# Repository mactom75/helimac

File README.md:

<p align="center">
  <a href="https://helimac.pl/en/">
    <picture>
      <source media="(prefers-color-scheme: dark)" srcset="website/assets/img/logo-dark-600.webp">
      
    </picture>
  </a>
</p>

<p align="center"><b>Open-source single-seat electric helicopter</b><br>
coaxial rotors · weight-shift control · 400 V electric drive · built in the open</p>

<p align="center">
  🇬🇧 English · <a href="README.pl.md">🇵🇱 Polski</a> · 🌐 <a href="https://helimac.pl/en/">helimac.pl</a> · ▶️ <a href="https://www.youtube.com/@Helimac-pl">YouTube</a> · ☕ <a href="https://buycoffee.to/helimac">Support</a>
</p>

> **Current design: rev K — in design (update 26 Nov 2026: [motor B, rotor, drive, controls, inverter](docs/design-rev-K-2026-11-26.md)).** The machine was recalculated from scratch to cut the mass from 74.9 to ≈ 43.4 kg. Files in [`production/`](production/README.md) are **rev J2 — archive, do not build** (exception: MC-P inverter rev D1 is current). Rev K production packages will follow after stage 3 (CAD + drawings).

---

## Start here

| I want to… | Go to |
|---|---|
| 👀 **see the design** | [Design rev K](docs/design-rev-K.md) + [update 26 Nov](docs/design-rev-K-2026-11-26.md) · [drawings 26 Nov](docs/graphics/revK/2026-11-26/) · [graphics](docs/graphics/revK/) · [layout sketch](docs/graphics/HELIMAC_revK_szkic_ukladu.pdf) · [parameters](docs/parameters.md) · [website](https://helimac.pl/en/) |
| 📦 **download the files** | rev K: [calculations](calc/revK/), [drawings (PDF)](docs/graphics/revK/2026-11-26/), [blade templates (DXF)](hardware/blades/revK-templates/) · rev J2 (archive): [release](../../releases/latest), [production files](production/) · MC-P inverter rev D1 (current): [files](production/electronics/MC-P-inverter-revD1/) |
| 🛠️ **help build it** | [Open tasks (Issues)](../../issues) · [Discussions](../../discussions) · [How to contribute](CONTRIBUTING.md) |
| ▶️ **follow the build** | [YouTube @Helimac-pl](https://www.youtube.com/@Helimac-pl) · [build log](BUILD_LOG.md) · [roadmap](ROADMAP.md) |
| ☕ **support the project** | [buycoffee.to/helimac](https://buycoffee.to/helimac) — every coffee goes to parts and dynamometer tests |

> ⚠️ **Prototype in design — not an approved aircraft.** All values are calculated, not yet measured. Read [SAFETY.md](SAFETY.md) before building anything.

<p align="center">
  <br>
  <sub>HELIMAC rev K — complete machine (concept model): coaxial rotors Ø 4.5 m, belt drive above the pilot, frame of three aluminium tubes · <a href="docs/graphics/HELIMAC_revK_szkic_ukladu.pdf">layout sketch with dimensions</a> · <a href="docs/graphics/revK/">all rev K graphics</a></sub>
</p>

## What is HELIMAC?

A light, single-seat helicopter with a fully electric drive, designed openly with contributors from around the world. Every drawing, calculation, piece of software, test result — and mistake — is published here.

The name combines **HELI**copter and **MAC**iąg — the surname of the founder, **Tomasz Maciąg** from Bydgoszcz, Poland. It continues his original **HeliMac** project (2013–2015), now redesigned from scratch with the help of AI tools. **[Read the story →](ABOUT.md)**

Target category: single-seat ultralight helicopter, MTOM ≤ 300 kg ([Annex I to Regulation (EU) 2018/1139](docs/regulations.md) — national rules instead of EASA certification).

## Current design — rev K (in design)

| | |
|---|---|
| Configuration | coaxial, 2 × 2-blade rotors Ø 4.5 m, 500 rpm, no tail rotor |
| Control | direction by pilot weight shift (no cyclic) · collective by electric actuators · yaw by upper/lower collective difference |
| Pilot | up to 110 kg |
| Take-off mass | ≈ 193 kg (machine without battery ≈ 43.4 kg, battery 40 kg) |
| Hover power | ≈ 16–16.6 kW (1.3 g on a hot day: ≈ 25 kW) |
| Drive | **motor B**: 30 kW continuous, 10 000 rpm, outer rotor with Halbach magnets, ≈ 6 kg → **toothed-belt drive 20:1** (carbon-cord belts, one-way clutch for autorotation, no oil) → coaxial shafts |
| Blades | VR-7 airfoil with trailing-edge tab, foam core, carbon D-spar and skin, tungsten tip mass, ≈ 2.04 kg each |
| Frame | three Al 7075-T6 tubes: two front legs (triangle) + one curved rear leg with seat, footrest and battery |
| Electronics | in-house SiC inverter **MC-P** rev D1 (KiCad) · control board **MC-C** in design |
| Battery | 112S4P Li-ion, ≈ 400 V, ≈ 8 kWh, 40 kg |
| Flight time (calc.) | ≈ 21 min hover / ≈ 28–29 min mixed |
| **Current stage** | **rev K stage 3 — CAD model and drawings**, then production packages and the dynamometer |

Previous version: [rev J2](docs/design-rev-J2.md) (archive) — 74.9 kg without battery, cycloidal + bevel gearbox.

## What's where

| Folder | Inside |
|---|---|
| [production/](production/) | production files — **rev J2 archive** (J1, J2, J3: do not build) and **MC-P inverter rev D1 (current)** |
| [hardware/](hardware/) | assembly overviews with CAD graphics: frame, seat, rotor head & controls, blades, transmission, motor |
| [electronics/](electronics/) | MC-P inverter, MC-C controller, battery + BMS, avionics |
| [docs/](docs/) | [design rev K](docs/design-rev-K.md), [rev J2 (archive)](docs/design-rev-J2.md), parameters, regulations, [graphics (PDF)](docs/graphics/) |
| [calc/](calc/) | performance calculator and [rev K design calculations](calc/revK/) (Python) |
| [firmware/](firmware/) | software (to come) |

## Get involved

We especially welcome aircraft structural engineers, rotor and flight-dynamics specialists, power-electronics and battery engineers, helicopter pilots, aircraft mechanics, makers with 3D printers and CNC, and people who know light-aircraft rules in their country.

1. **Say hello** in [Discussions](../../discussions).
2. **Pick a task** from [Issues](../../issues) — e.g. [#1 400 V inverter review](../../issues/1) or [#6 calculator](../../issues/6) (good first issue).
3. **Read** [CONTRIBUTING.md](CONTRIBUTING.md) and [SAFETY.md](SAFETY.md).

English is the main project language; Polish is equally welcome.

## Licences

Hardware: [CERN-OHL-S-2.0](LICENSES/CERN-OHL-S-2.0.txt) · Software: [GPL-3.0-or-later](LICENSES/GPL-3.0-or-later.txt) · Documentation: [CC-BY-SA-4.0](LICENSES/CC-BY-SA-4.0.txt) · The HELIMAC name and logo are not covered by these licences ([branding/](branding/)). Provided **without any warranty** — see [LICENSE](LICENSE).

---

**Founder & maintainer:** Tomasz Maciąg · Bydgoszcz, Poland · [helimac.pl](https://helimac.pl/en/)

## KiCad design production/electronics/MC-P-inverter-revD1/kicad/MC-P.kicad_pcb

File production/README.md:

# HELIMAC — production files (rev J2)

Polska wersja: [README.pl.md](README.pl.md)

> 🛑 **Rev J2 is an archive version — do not manufacture J1, J2 or J3.** The current design is **rev K** (in design, [docs/design-rev-K.md](../docs/design-rev-K.md)); rev K production packages will follow after stage 3 (CAD + drawings). **Exception: the MC-P inverter rev D1 is current** and stays in rev K.

Everything needed to manufacture design rev J2 (archive; pilot up to 110 kg, MTOW 225 kg): drawings, DXF cutting files, STEP models, 3D-print STL files, blade CNC data, and the complete KiCad project of the MC-P inverter with Gerbers, BOM and placement files.

> ⚠️ **Prototype, not an approved aircraft.** All values are calculated, not yet measured. Read [SAFETY.md](../SAFETY.md) before building anything. Build and test in stages: drive on the test bench first (395 N·m / 30 min, then 50 h), then tethered rotor tests, then uncrewed flights. Have drawings and the 400 V electronics reviewed by qualified engineers before you make parts.

## Download

The four ZIP files are complete packages, including the STEP and STL files:

| Package | Contents | File |
|---|---|---|
| **J1 – Drive unit rev J2** | motor, cycloidal transmission 10:1, reversing bevel gearbox, rotor hubs, upper collective, bearings | [HELIMAC_J1_drive_revJ2.zip](downloads/HELIMAC_J1_drive_revJ2.zip) (32 MB) |
| **J2 – Rotor blades rev J** | 4 blades (lower D + mirrored upper G), 3D-printed ASA cores, jigs, CNC sections | [HELIMAC_J2_blades_revJ.zip](downloads/HELIMAC_J2_blades_revJ.zip) (16 MB) |
| **J3 – Frame, seat, air-guide ring, lower collective rev J2** | frame, seat with harness points, PK ring segments, lower collective | [HELIMAC_J3_frame_seat_revJ2.zip](downloads/HELIMAC_J3_frame_seat_revJ2.zip) (0.6 MB) |
| **MC-P – 3-phase SiC inverter rev D1** | KiCad 7 project, Gerbers, BOM, CPL, schematic, mechanical drawing, STEP | [HELIMAC_MC-P_inverter_revD1.zip](downloads/HELIMAC_MC-P_inverter_revD1.zip) (2.6 MB) |

To download a ZIP, open its link and click **Download raw file** (↓). To get the whole repository, use **Code → Download ZIP** on the main page.

The drawings, DXF, Gerber and KiCad files are also in the folders below, so you can browse them on GitHub. Each STEP and STL set is only in its ZIP; the drive assembly STEP alone is 107 MB.

Documentation language: Polish (drawings, notes, file names). Part numbers are consistent across all packages: K = column, P = cycloidal transmission, N = reversing gearbox / upper hub, S = motor, C = collective, R = frame/seat, PK = air-guide ring, L/W/J = blade segments, blade drawings, jigs.

## Mechanical — [mechanical/](mechanical/)

### J1 – Drive unit rev J2 — [J1-drive-revJ2/](mechanical/J1-drive-revJ2/)
- `drawings/ZS-00_zlozeniowy_revJ.pdf` — general assembly with full parts list (materials, quantities, standard parts, bearings).
- `drawings/Helimac_revJ_rysunki_czesci.pdf` — part drawings: dimensions, tolerances, heat treatment, surface finish.
- `drawings/MT_rysunki_montazowe_revJ.pdf` — assembly sequence drawings (motor, transmission, hubs, column, frame interface).
- `drawings/ECN-J01…`, `ECN-J03…` — change notes rev H → J → J2 (110 kg pilot, bearings).
- `dxf/` — 2D cutting files with material and quantity in the file name: motor laminations S01/S02 (NO20 0.20 mm, 280 + 280 pcs; order 285 + 285), cycloidal cams P01 (100Cr6), plates and rings (Al 7075-T651), shims (CuSn8), coupling insert P11.
- ZIP only: `step/` — 41 part models and the complete drive assembly `ZESPOL_Helimac_naped_revJ.step`.

### J2 – Rotor blades rev J — [J2-blades-revJ/](mechanical/J2-blades-revJ/)
- `00_SPIS_ZESTAWU_LOPATY_Helimac_revJ.pdf` — package index; `Helimac_WL-01_lopaty_dokumentacja_revJ.pdf` — manufacturing process: cores, carbon layup, balancing, root, inspection.
- `01_RYSUNKI/` — blade drawings W-00…W-05, lower (D) and upper (G, mirrored).
- `03_DANE_CNC/` — outer section coordinates (CSV) for D and G, clamping plate W-07 (DXF).
- `04_ANALIZA/` — DY-02 coaxial rotor analysis (performance, loads, vibration, Campbell diagram).
- `05_INTERFEJS_PIASTY/` — hub interface drawings (P07, N05, C03, C04).
- ZIP only: `02_STL_DO_DRUKU/` — ASA core segments L00–L09, lay-up beds J1, angle gauges J2, root drilling jig J3, for D and G.

### J3 – Frame, seat, PK ring, lower collective rev J2 — [J3-frame-seat-revJ2/](mechanical/J3-frame-seat-revJ2/)
- `01_RYSUNKI/Helimac_R_rysunki_rama_kolektyw_revJ.pdf` — frame, seat, lower collective drawings.
- ECN-J02, ECN-J03 — change notes.
- ZIP only: `02_STEP/` (frame and seat assemblies, parts, servo, inverter envelope), `03_STL_PK_DO_DRUKU/` (air-guide ring in 6 printable segments).
- ⚠️ **The frame layout may change.** A new layout (hang-glider style front triangle and a single rear leg) is being calculated. Do not make frame tubes yet; the seat and collective parts are not affected.

## Electronics — [electronics/](electronics/)

### MC-P – 3-phase SiC inverter rev D1 — [MC-P-inverter-revD1/](electronics/MC-P-inverter-revD1/)
400 V DC, 6 × SiC MOSFET C3M0016120K (1200 V, 16 mΩ), isolated gate drivers with DESAT short-circuit protection. Board: 215 × 116 mm, 4 layers, 2 oz copper.
- `kicad/` — KiCad 7 project (`MC-P.kicad_pro`, schematic, routed PCB, design rules with 400 V clearances, custom footprints in `lib/`).
- `fabrication/` — Gerbers and drill files (`gerber/` and ZIP), BOM and pick-and-place files (`*_BOM_*.csv`, `*_CPL_*.csv`, LCSC part numbers), fabrication and assembly notes `CZYTAJ_produkcja_i_montaz_revD1.txt`.
- `docs/` — schematic PDF, mechanical drawing (heatsink, clips, mounting), copper layer prints, 3D model `MC-P.step`, renders, DRC report, heatsink calculation.
- Fabrication: 4 layers, 1.6 mm, FR-4 TG155+, 2 oz outer and inner copper, ENIG, electrical test. Through-hole SiC transistors go on the bottom side, metal tab down onto the heatsink (AlN/Al₂O₃ pad + paste, spring clip). Film capacitors C61–C64 and M5 terminals are fitted by hand.
- Before powering: 1.5 kV DC hipot (400 V side vs. low-voltage side and heatsink, < 1 mA), first power-up from a current-limited supply.
- The control board MC-C is still in design ([../electronics/mc-c-controller/](../electronics/mc-c-controller/)).

## Open items (not yet in these files)
- New frame layout (see J3).
- Collective on the lower rotor: being decided whether it keeps variable pitch (currently 3 servos) — affects the lower collective parts in J3.
- MC-C control board, battery pack and BMS.
- Onshape source models will be linked when published.

## Licence
Hardware: CERN-OHL-S-2.0 · Documentation: CC-BY-SA-4.0 · © Tomasz Maciąg and HELIMAC contributors. The HELIMAC name and logo are not covered by these licences ([branding/](../branding/)).

Questions and corrections: [Issues](https://github.com/mactom75/helimac/issues) / [Discussions](https://github.com/mactom75/helimac/discussions).

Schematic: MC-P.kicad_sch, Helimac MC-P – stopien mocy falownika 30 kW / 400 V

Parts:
C1, C9, C21, C29, C41, C49: 47pF 0603; C_0603_1608Metric; LCSC C1671
C2, C10, C22, C30, C42, C50, C73: 1uF 0603; C_0603_1608Metric; LCSC C15849
C3, C11, C19, C23, C31, C39, C43, C51, C59, C67, C69, C70: 100nF 0603; C_0603_1608Metric; LCSC C14663
C4, C6, C8, C12, C14, C16, C24, C26, C28, C32, C34, C36, C44, C46, C48, C52, C54, C56, C65, C66, C71, C72: 10uF 25V 1206; C_1206_3216Metric; LCSC C13585
C5, C7, C13, C15, C25, C27, C33, C35, C45, C47, C53, C55: 1uF 25V 0603; C_0603_1608Metric; LCSC C15849
C17, C18, C37, C38, C57, C58: 100nF 1kV X7R 1812; C_1812_4532Metric; LCSC C106147
C20, C40, C60: 1nF 0603; C_0603_1608Metric; LCSC C1588
C61, C62, C63, C64: 10uF 800V film; C_Rect_L32.0mm_W22.0mm_P27.50mm_Film; LCSC C328820
C68: 100pF 0603; C_0603_1608Metric; LCSC C14858
D1, D2, D3, D4, D5, D6, D7, D8, D9, D10, D11, D12: RS1M 1000V; D_SMA; LCSC C115427
H1, H2, H3, H4, H5, H6, H7, H8: M3 montaż; MountingHole_3.2mm_M3
J1: Faza A M5; MountingHole_5.3mm_M5_Pad_Via
J2: Faza B M5; MountingHole_5.3mm_M5_Pad_Via
J3: Faza C M5; MountingHole_5.3mm_M5_Pad_Via
J4: DC+ M5; MountingHole_5.3mm_M5_Pad_Via
J5: DC- M5; MountingHole_5.3mm_M5_Pad_Via
J6: IDC 2x20 do MC-C; IDC-Header_2x20_P2.54mm_Vertical; LCSC C9138
J7: NTC radiatora 2x; JST_XH_B4B-XH-A_1x04_P2.50mm_Vertical; LCSC C144395
PS1, PS2, PS3, PS4, PS5, PS6: QA151C3; SIP-7_QA151C3_P2.54mm; LCSC C7500962
Q1, Q2, Q3, Q4, Q5, Q6: C3M0016120K; TO-247-4_Horizontal_TabUp; LCSC C5713523
R1, R2, R5, R6, R9, R10, R13, R14, R17, R18, R21, R22: 4.7R 1206; R_1206_3216Metric; LCSC C17937
R3, R7, R11, R15, R19, R23: 10k 0603; R_0603_1608Metric; LCSC C25804
R4, R8, R12, R16, R20, R24: 1k 0603; R_0603_1608Metric; LCSC C21190
R25, R26, R27, R28, R29, R30: 15k 2512; R_2512_6332Metric; LCSC C81251
R31: 100k 0603; R_0603_1608Metric; LCSC C25803
R32, R33, R34, R35: 1M 1206 1%; R_1206_3216Metric; LCSC C17927
R36: 16k 0603 0.1%; R_0603_1608Metric; LCSC C326732
U1, U2, U4, U5, U7, U8: UCC21750QDWRQ1; SOIC-16W_7.5x10.3mm_P1.27mm; LCSC C2868955
U3, U6, U9: ACS758KCB-150B-PFF-T; Allegro_CB_PFF; LCSC C963431
U10: UCC12050DVER; SOIC-16W_7.5x10.3mm_P1.27mm; LCSC C504571
U11: AMC1311BDWVR; SOIC-8W_7.5x5.85mm_P1.27mm_DWV; LCSC C783598

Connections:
+3V3: C70.1, C73.1, J6.7, U11.8 (VDD2)
+5V: C2.1, C3.1, C10.1, C11.1, C19.1, C22.1, C23.1, C30.1, C31.1, C39.1, C42.1, C43.1, C50.1, C51.1, C59.1, C65.1, C72.1, J6.5, J6.6, R31.2, U1.15 (VCC), U2.15 (VCC), U3.1 (VCC), U4.15 (VCC), U5.15 (VCC), U6.1 (VCC), U7.15 (VCC), U8.15 (VCC), U9.1 (VCC), U10.1 (EN), U10.3 (VINP)
+5V_HV: C66.1, C67.1, C69.1, U10.13 (SEL), U10.14 (VISO), U11.1 (VDD1)
+15V: C8.1, C16.1, C28.1, C36.1, C48.1, C56.1, C71.1, J6.1, J6.2, PS1.1 (Vin), PS2.1 (Vin), PS3.1 (Vin), PS4.1 (Vin), PS5.1 (Vin), PS6.1 (Vin)
BLD1: R25.2, R26.1
BLD2: R26.2, R27.1
BLD3: R27.2, R28.1
BLD4: R28.2, R29.1
BLD5: R29.2, R30.1
DC+: C17.1, C18.1, C37.1, C38.1, C57.1, C58.1, C61.1, C62.1, C63.1, C64.1, D2.1 (K), D6.1 (K), D10.1 (K), J4.1, Q1.1 (D), Q3.1 (D), Q5.1 (D), R25.1, R32.1
DC-: C17.2, C18.2, C37.2, C38.2, C57.2, C58.2, C61.2, C62.2, C63.2, C64.2, C66.2, C67.2, C68.2, C69.2, J5.1, Q2.2 (S), Q4.2 (S), Q6.2 (S), R30.2, R36.2, U10.9 (GNDS), U10.10 (NC), U10.11 (NC), U10.12 (NC), U10.15 (GNDS), U10.16 (GNDS), U11.3 (SHTDN), U11.4 (GND1)
DSAT_AH: C1.1, R4.1, U1.2 (DESAT)
DSAT_AL: C9.1, R8.1, U2.2 (DESAT)
DSAT_BH: C21.1, R12.1, U4.2 (DESAT)
DSAT_BL: C29.1, R16.1, U5.2 (DESAT)
DSAT_CH: C41.1, R20.1, U7.2 (DESAT)
DSAT_CL: C49.1, R24.1, U8.2 (DESAT)
DSM_AH: D1.1 (K), D2.2 (A)
DSM_AL: D3.1 (K), D4.2 (A)
DSM_BH: D5.1 (K), D6.2 (A)
DSM_BL: D7.1 (K), D8.2 (A)
DSM_CH: D9.1 (K), D10.2 (A)
DSM_CL: D11.1 (K), D12.2 (A)
DSR_AH: D1.2 (A), R4.2
DSR_AL: D3.2 (A), R8.2
DSR_BH: D5.2 (A), R12.2
DSR_BL: D7.2 (A), R16.2
DSR_CH: D9.2 (A), R20.2
DSR_CL: D11.2 (A), R24.2
GND: C2.2, C3.2, C8.2, C10.2, C11.2, C16.2, C19.2, C20.2, C22.2, C23.2, C28.2, C30.2, C31.2, C36.2, C39.2, C40.2, C42.2, C43.2, C48.2, C50.2, C51.2, C56.2, C59.2, C60.2, C65.2, C70.2, C71.2, C72.2, C73.2, J6.3, J6.4, J6.8, J6.10, J6.12, J6.14, J6.15, J6.17, J6.18, J6.19, J6.20, J6.24, J6.28, J6.31, J6.32, J6.33, J6.34, J6.35, J6.36, J7.2, J7.4, PS1.2 (GND), PS2.2 (GND), PS3.2 (GND), PS4.2 (GND), PS5.2 (GND), PS6.2 (GND), U1.9 (GND), U1.11 (IN-), U2.9 (GND), U2.11 (IN-), U3.2 (GND), U4.9 (GND), U4.11 (IN-), U5.9 (GND), U5.11 (IN-), U6.2 (GND), U7.9 (GND), U7.11 (IN-), U8.9 (GND), U8.11 (IN-), U9.2 (GND), U10.2 (GNDP), U10.4 (SYNC), U10.6 (NC), U10.7 (NC), U10.8 (NC), U11.5 (GND2)
G_AH: Q1.4 (G), R1.2, R2.2, R3.1, U1.7 (CLMPI)
G_AL: Q2.4 (G), R5.2, R6.2, R7.1, U2.7 (CLMPI)
G_BH: Q3.4 (G), R9.2, R10.2, R11.1, U4.7 (CLMPI)
G_BL: Q4.4 (G), R13.2, R14.2, R15.1, U5.7 (CLMPI)
G_CH: Q5.4 (G), R17.2, R18.2, R19.1, U7.7 (CLMPI)
G_CL: Q6.4 (G), R21.2, R22.2, R23.1, U8.7 (CLMPI)
IPH_A: C20.1, J6.25, U3.3 (VIOUT)
IPH_B: C40.1, J6.26, U6.3 (VIOUT)
IPH_C: C60.1, J6.27, U9.3 (VIOUT)
KS_AH: C1.2, C4.2, C5.2, C6.1, C7.1, PS1.6 (0V), Q1.3 (KS), R3.2, U1.1 (AIN), U1.3 (COM)
KS_AL: C9.2, C12.2, C13.2, C14.1, C15.1, PS2.6 (0V), Q2.3 (KS), R7.2, U2.1 (AIN), U2.3 (COM)
KS_BH: C21.2, C24.2, C25.2, C26.1, C27.1, PS3.6 (0V), Q3.3 (KS), R11.2, U4.1 (AIN), U4.3 (COM)
KS_BL: C29.2, C32.2, C33.2, C34.1, C35.1, PS4.6 (0V), Q4.3 (KS), R15.2, U5.1 (AIN), U5.3 (COM)
KS_CH: C41.2, C44.2, C45.2, C46.1, C47.1, PS5.6 (0V), Q5.3 (KS), R19.2, U7.1 (AIN), U7.3 (COM)
KS_CL: C49.2, C52.2, C53.2, C54.1, C55.1, PS6.6 (0V), Q6.3 (KS), R23.2, U8.1 (AIN), U8.3 (COM)
NTC1: J6.37, J7.1
NTC2: J6.38, J7.3
OUTH_AH: R1.1, U1.4 (OUTH)
OUTH_AL: R5.1, U2.4 (OUTH)
OUTH_BH: R9.1, U4.4 (OUTH)
OUTH_BL: R13.1, U5.4 (OUTH)
OUTH_CH: R17.1, U7.4 (OUTH)
OUTH_CL: R21.1, U8.4 (OUTH)
OUTL_AH: R2.1, U1.6 (OUTL)
OUTL_AL: R6.1, U2.6 (OUTL)
OUTL_BH: R10.1, U4.6 (OUTL)
OUTL_BL: R14.1, U5.6 (OUTL)
OUTL_CH: R18.1, U7.6 (OUTL)
OUTL_CL: R22.1, U8.6 (OUTL)
PH_A: J1.1, U3.5 (IP-)
PH_B: J2.1, U6.5 (IP-)
PH_C: J3.1, U9.5 (IP-)
PWM_AH: J6.9, U1.10 (IN+)
PWM_AL: J6.11, U2.10 (IN+)
PWM_BH: J6.13, U4.10 (IN+)
PWM_BL: J6.16, U5.10 (IN+)
PWM_CH: J6.40, U7.10 (IN+)
PWM_CL: J6.39, U8.10 (IN+)
RDY: J6.22, U1.12 (RDY), U2.12 (RDY), U4.12 (RDY), U5.12 (RDY), U7.12 (RDY), U8.12 (RDY)
SW_A: D4.1 (K), Q1.2 (S), Q2.1 (D), U3.4 (IP+)
SW_B: D8.1 (K), Q3.2 (S), Q4.1 (D), U6.4 (IP+)
SW_C: D12.1 (K), Q5.2 (S), Q6.1 (D), U9.4 (IP+)
SYNCOK: R31.1, U10.5 (SYNC_OK)
VD1_BUS: R32.2, R33.1
VD2_BUS: R33.2, R34.1
VD3_BUS: R34.2, R35.1
VDD_AH: C4.1, C5.1, PS1.5 (+Vo), U1.5 (VDD)
VDD_AL: C12.1, C13.1, PS2.5 (+Vo), U2.5 (VDD)
VDD_BH: C24.1, C25.1, PS3.5 (+Vo), U4.5 (VDD)
VDD_BL: C32.1, C33.1, PS4.5 (+Vo), U5.5 (VDD)
VDD_CH: C44.1, C45.1, PS5.5 (+Vo), U7.5 (VDD)
VDD_CL: C52.1, C53.1, PS6.5 (+Vo), U8.5 (VDD)
VEE_AH: C6.2, C7.2, PS1.7 (-Vo), U1.8 (VEE)
VEE_AL: C14.2, C15.2, PS2.7 (-Vo), U2.8 (VEE)
VEE_BH: C26.2, C27.2, PS3.7 (-Vo), U4.8 (VEE)
VEE_BL: C34.2, C35.2, PS4.7 (-Vo), U5.8 (VEE)
VEE_CH: C46.2, C47.2, PS5.7 (-Vo), U7.8 (VEE)
VEE_CL: C54.2, C55.2, PS6.7 (-Vo), U8.8 (VEE)
VIN_BUS: C68.1, R35.2, R36.1, U11.2 (VIN)
VON_BUS: J6.30, U11.6 (VOUTN)
VOP_BUS: J6.29, U11.7 (VOUTP)
nFLT: J6.21, U1.13 (~FLT), U2.13 (~FLT), U4.13 (~FLT), U5.13 (~FLT), U7.13 (~FLT), U8.13 (~FLT)
nRST: J6.23, U1.14 (RST/EN), U2.14 (RST/EN), U4.14 (RST/EN), U5.14 (RST/EN), U7.14 (RST/EN), U8.14 (RST/EN)

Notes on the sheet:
CONN
ISO
DCLINK
TERM
POW_A
POW_B
POW_C
CS_A
CS_B
CS_C
GD_AH
GD_AL
GD_BH
GD_BL
GD_CH
GD_CL
VM_BUS

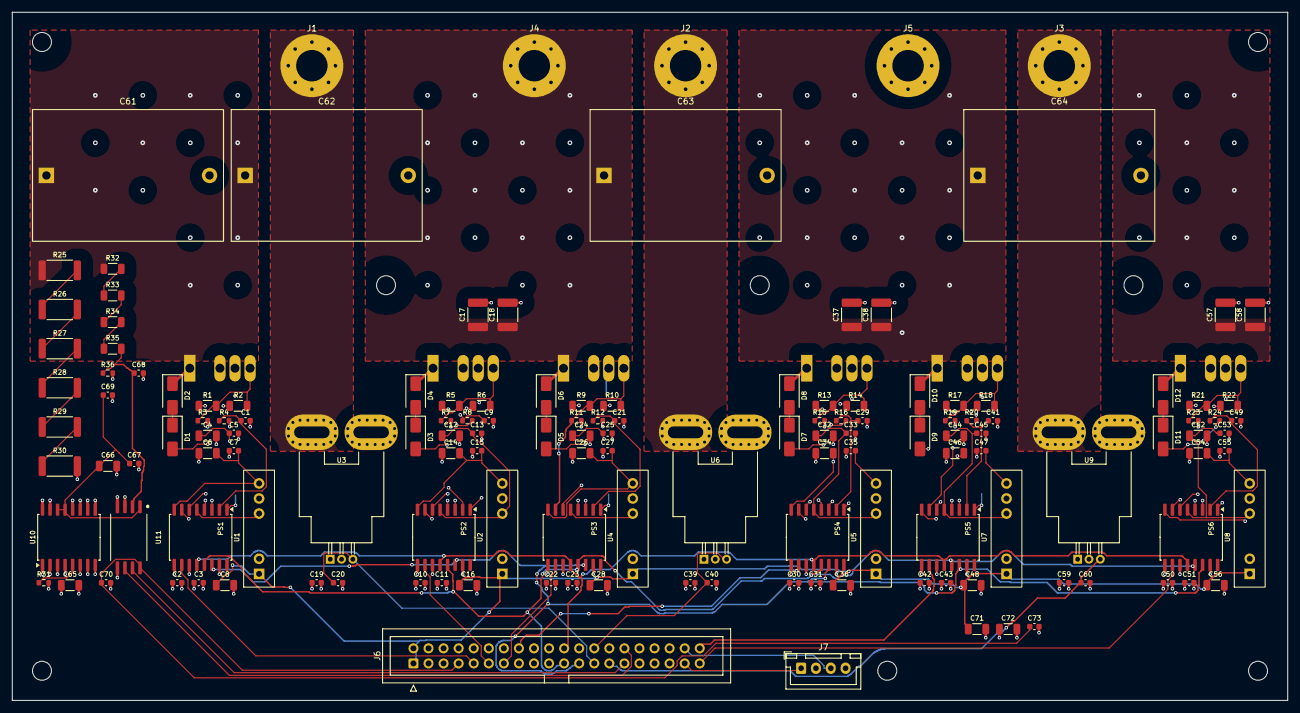
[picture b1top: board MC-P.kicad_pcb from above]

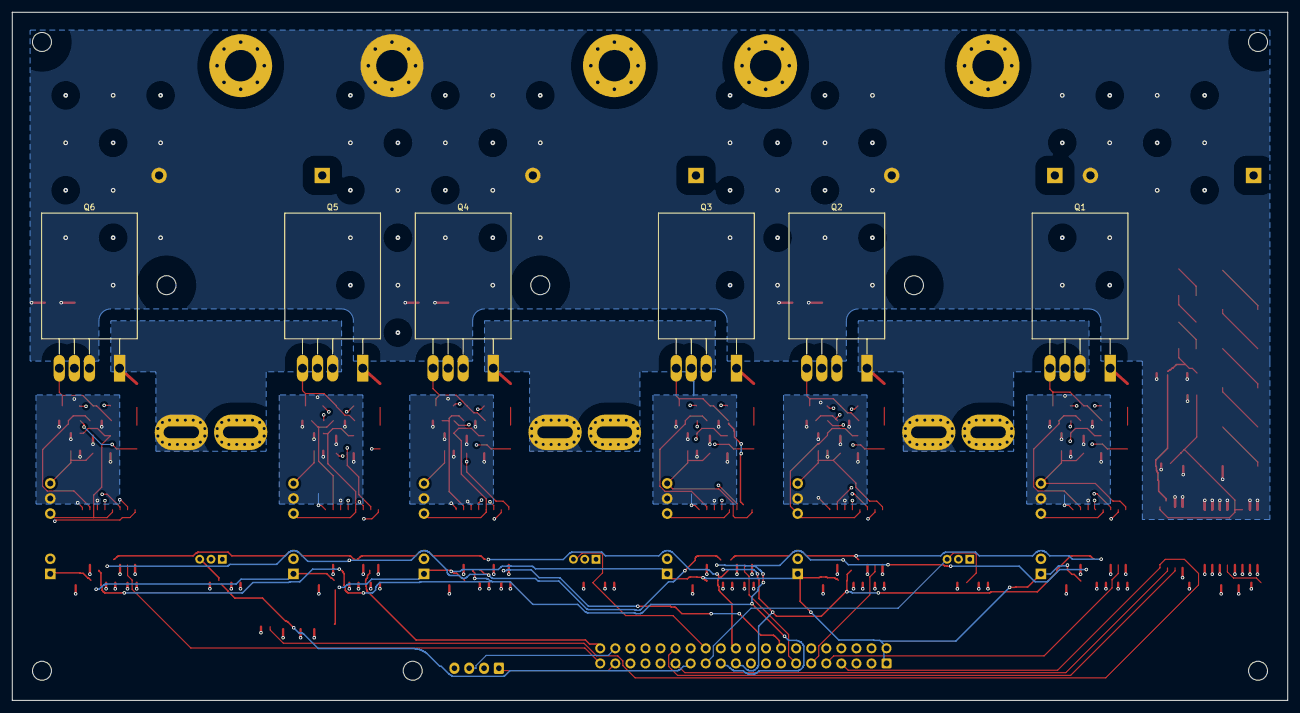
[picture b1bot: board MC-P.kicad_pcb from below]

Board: 4 copper layers, 215.0 x 116.0 mm, 159 parts (6 on the bottom side), 93 nets.

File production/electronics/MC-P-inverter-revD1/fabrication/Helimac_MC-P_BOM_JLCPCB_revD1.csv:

Comment,Designator,Footprint,LCSC Part #,Qty,Uwagi
47pF 0603,"C1,C9,C21,C29,C41,C49",C_0603_1608Metric,C1671,6,czas wygaszania DESAT
1uF 0603,"C2,C10,C22,C30,C42,C50,C73",C_0603_1608Metric,C15849,7,
100nF 0603,"C3,C11,C19,C23,C31,C39,C43,C51,C59,C67,C69,C70",C_0603_1608Metric,C14663,12,
10uF 25V 1206,"C4,C6,C8,C12,C14,C16,C24,C26,C28,C32,C34,C36,C44,C46,C48,C52,C54,C56,C65,C66,C71,C72",C_1206_3216Metric,C13585,22,
1uF 25V 0603,"C5,C7,C13,C15,C25,C27,C33,C35,C45,C47,C53,C55",C_0603_1608Metric,C15849,12,
100nF 1kV X7R 1812,"C17,C18,C37,C38,C57,C58",C_1812_4532Metric,C106147,6,odsprzęganie gałęzi – tuż przy tranzystorach
1nF 0603,"C20,C40,C60",C_0603_1608Metric,C1588,3,
10uF 800V film,"C61,C62,C63,C64",C_Rect_L32.0mm_W22.0mm_P27.50mm_Film,C328820,4,
100pF 0603,C68,C_0603_1608Metric,C14858,1,
RS1M 1000V,"D1,D2,D3,D4,D5,D6,D7,D8,D9,D10,D11,D12",D_SMA,C115427,12,DESAT – 2 diody 1000 V w szeregu
IDC 2x20 do MC-C,J6,IDC-Header_2x20_P2.54mm_Vertical,C9138,1,
NTC radiatora 2x,J7,JST_XH_B4B-XH-A_1x04_P2.50mm_Vertical,C144395,1,
QA151C3,"PS1,PS2,PS3,PS4,PS5,PS6",SIP-7_QA151C3_P2.54mm,C7500962,6,
C3M0016120K,"Q1,Q2,Q3,Q4,Q5,Q6",TO-247-4_Horizontal_TabUp,C5713523,6,"rev J: 16 mΩ zamiast 21 mΩ – ten sam footprint TO-247-4"
4.7R 1206,"R1,R2,R5,R6,R9,R10,R13,R14,R17,R18,R21,R22",R_1206_3216Metric,C17937,12,Rg wł.
10k 0603,"R3,R7,R11,R15,R19,R23",R_0603_1608Metric,C25804,6,ściąganie bramki
1k 0603,"R4,R8,R12,R16,R20,R24",R_0603_1608Metric,C21190,6,DESAT
15k 2512,"R25,R26,R27,R28,R29,R30",R_2512_6332Metric,C81251,6,rozładowanie szyny
100k 0603,R31,R_0603_1608Metric,C25803,1,
1M 1206 1%,"R32,R33,R34,R35",R_1206_3216Metric,C17927,4,dzielnik HV (≤ 125 V na rezystor)
16k 0603 0.1%,R36,R_0603_1608Metric,C326732,1,
UCC21750QDWRQ1,"U1,U2,U4,U5,U7,U8",SOIC-16W_7.5x10.3mm_P1.27mm,C2868955,6,AIN do COM (nieużywane)
ACS758KCB-150B-PFF-T,"U3,U6,U9",Allegro_CB_PFF,C963431,3,
UCC12050DVER,U10,SOIC-16W_7.5x10.3mm_P1.27mm,C504571,1,
AMC1311BDWVR,U11,SOIC-8W_7.5x5.85mm_P1.27mm_DWV,C783598,1,
